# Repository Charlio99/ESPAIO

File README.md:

# ESPAIO-Mini
Home automation board based on ESP8266. Ready to fit in EU light switch boxes

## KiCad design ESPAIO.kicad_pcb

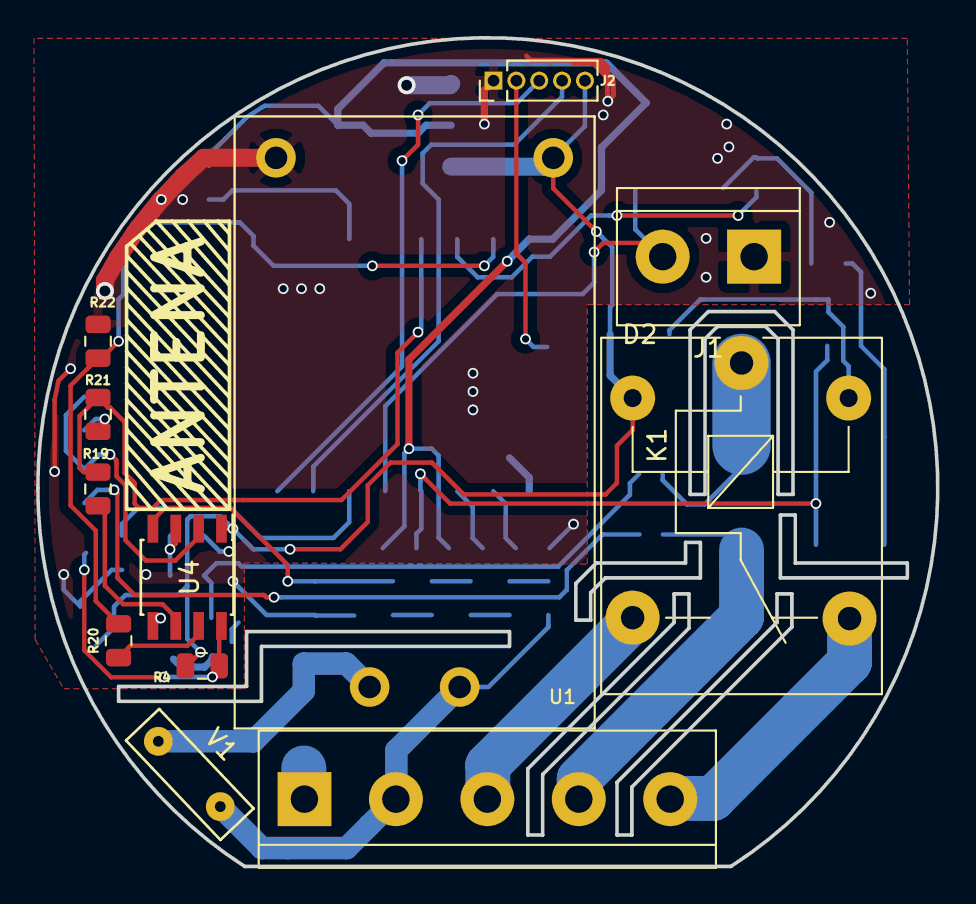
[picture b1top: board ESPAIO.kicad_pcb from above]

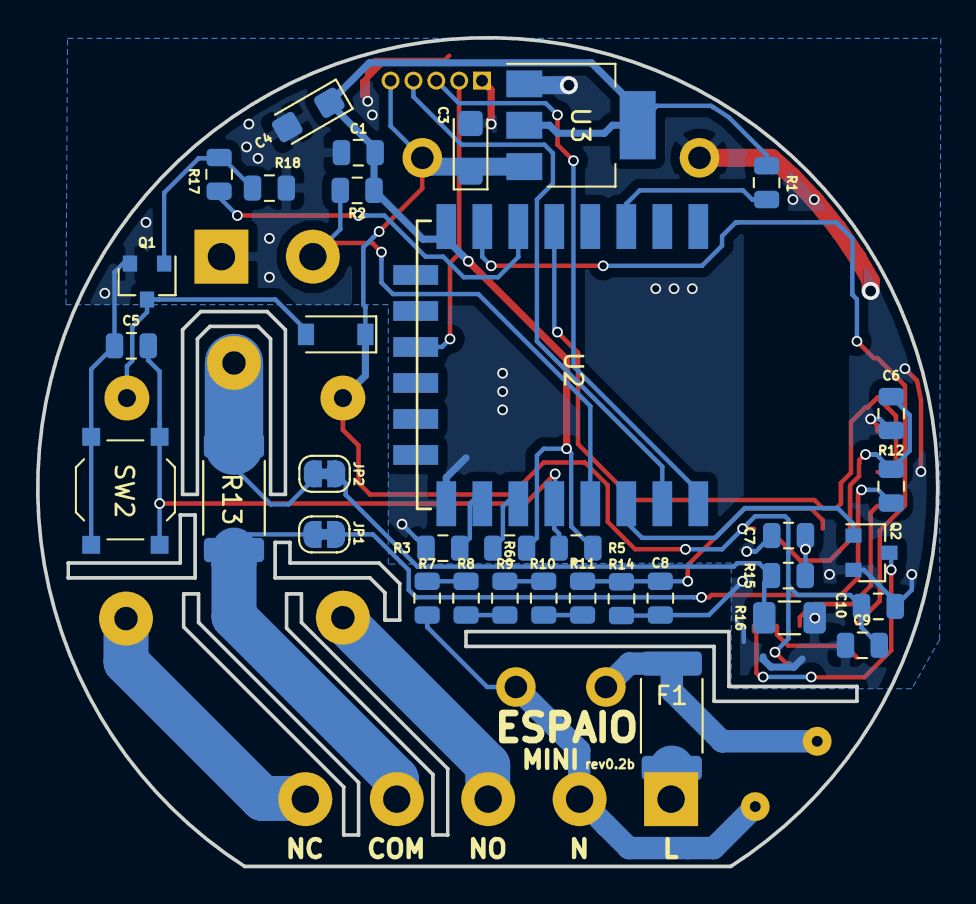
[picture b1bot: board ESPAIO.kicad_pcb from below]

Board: 2 copper layers, 50.0 x 46.0 mm, 47 parts (35 on the bottom side), 36 nets.

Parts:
C1, C5, C8, C10: 100nF; C_0805_2012Metric
C3, C4: 10uF; CP_EIA-3216-12_Kemet-S
C6, C7: 33nF; C_0805_2012Metric
C9: 1uF; C_0805_2012Metric
D2: 1N4148; D_SOD-123
F1: SF-2410FP050W-2; Fuse_2512_6332Metric
J1: WALL_SW; TerminalBlock_bornier-2_P5.08mm
J2: PROG; PinHeader_1x05_P1.27mm_Vertical
J3: Screw_Terminal_01x05; TerminalBlock_bornier-5_P5.08mm
JP1: LINE_I Jumper; SolderJumper-2_P1.3mm_Bridged_RoundedPad1.0x1.5mm
JP2: LINE_L Jumper; SolderJumper-2_P1.3mm_Bridged_RoundedPad1.0x1.5mm
K1: Relé; Relay_SPDT_SANYOU_SRD_Series_Form_C
Q1, Q2: 2N7002; SOT-23
R1, R2, R3, R4, R5, R6, R18, R19, R20: 10K; R_0805_2012Metric
R7, R8, R9, R10, R11: 470K; R_0805_2012Metric
R12, R14, R15, R17: 1K; R_0805_2012Metric
R13: R001; R_2512_6332Metric
R16: 0R; R_1206_3216Metric
R21, R22: 15K; R_0805_2012Metric
SW2: PROG_SWITCH; SW_SPST_TL3342
U1: HLK-PM01
U2: ESP-12E; ESP-12E_SMD
U3: AMS1117-3.3; SOT-223-3_TabPin2
U4: HLW8012; SOIC-8_3.9x4.9mm_P1.27mm
V1: Varistor; RV_Disc_D9mm_W3.3mm_P5mm

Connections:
+3V3: C1.1, C4.1, R1.2, R2.1, R5.1, R6.1, U2.8, U3.2
+5V: C3.1, C9.2, C10.2, D2.1, J2.5, K1.2, R4.2, U1.4, U3.3, U4.1
/CH_PD: R1.1, U2.3
/GPIO0: C5.2, R5.2, SW2.1, U2.12
/GPIO2: R6.2, U2.11
/GPIO4: J1.2, R2.2, U2.13
/GPIO5: Q2.1, U2.14
/GPIO9: J2.2, U2.19
/GPIO12: R17.2, U2.6
/GPIO13: R20.1, R22.2, U2.7
/GPIO14: R19.2, R21.2, U2.5
/GPIO15: R3.1, U2.10
/LINE_I: J3.4, JP1.2, R13.1
/LINE_L: JP2.2, K1.1, R13.2
/LIVE: F1.1, J3.1
/NC: J3.5, K1.4
/NEUTRAL: J3.2, R7.2, U1.2, V1.2
/NO: J3.3, K1.3
/RXD: J2.4, U2.15
/TXD: J2.3, U2.16
/V2P: C8.1, R11.1, R14.1, U4.4
GND: C1.2, C3.2, C4.2, C5.1, C6.2, C7.2, C8.2, C9.1, C10.1, J1.1, J2.1, Q1.2, Q2.2, R3.2, R14.2, R16.2, R18.1, R21.1, R22.1, SW2.2, U1.3, U2.9, U3.1, U4.5
unnamed: F1.2, U1.1, V1.1
unnamed: C6.1, R12.2, U4.2
unnamed: C7.1, R15.2, U4.3
unnamed: D2.2, K1.5, Q1.3
unnamed: JP1.1, R12.1
unnamed: JP2.1, R15.1, R16.1
unnamed: Q1.1, R17.1, R18.2
unnamed: Q2.3, R4.1, U4.8
unnamed: R7.1, R8.1
unnamed: R8.2, R9.2
unnamed: R9.1, R10.1
unnamed: R10.2, R11.2
unnamed: R19.1, U4.6
unnamed: R20.2, U4.7

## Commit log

2019-03-24 First commit. Actual version should be working. Any kind of fix, feature or doc will be commited and pushed ASAP. Also uploaded gerber files of older revisions.
